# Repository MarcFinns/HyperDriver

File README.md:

# HyperDriver
LED driver and power board for Hyperion (DYI Ambilight)

See short video: https://www.youtube.com/watch?v=JoaK5aRHBMA

After setting up hyperion I was annoyed by starting/stopping it manually every time.
My weekend project was to build a proper solution - with components I had in the drawer, which might explain some weird design choices.

The board does the following:

* Connects as a PI hat
* Powers the PI and the LED strip with the same power supply
* Provides 5V drivers / level adaptation for the APA 102 LED stripe
* Allows to turn the PI on by pushing a button
* With the same button, triggers a proper shutdown (no abrupt power cut)
* Connects to TV via USB and can start the PI when the TV turns on
* The PI can automatically shutdown when TV goes off (immediately or after X minutes)
* If the automatic turn on from TV is triggered, the PI can still be shut down via the button
* A 5V socket is available for a small fan, in case

The On/Off function is proper, meaning the power supply is truly disconnected from the mains when off.
I made sure that the PCB is single side and doable at home with some medium skills (e.g. i made it with toner transfer). 
I could not avoid one SMD but only because I did not have the through-hole part in the drawer. Convertinf the PCB to through hole is trivial.
The whole thing fits in a small electric junction box. See pictures.

**IMPORTANT DISCLAIMER:**<BR>
* This is **NOT** your typical 5V Arduino project. <BR>
* It is **NOT** breadboard friendly.<BR>
* Make it **ONLY** if you know what you are doing.<BR>
* Danger of electrocution

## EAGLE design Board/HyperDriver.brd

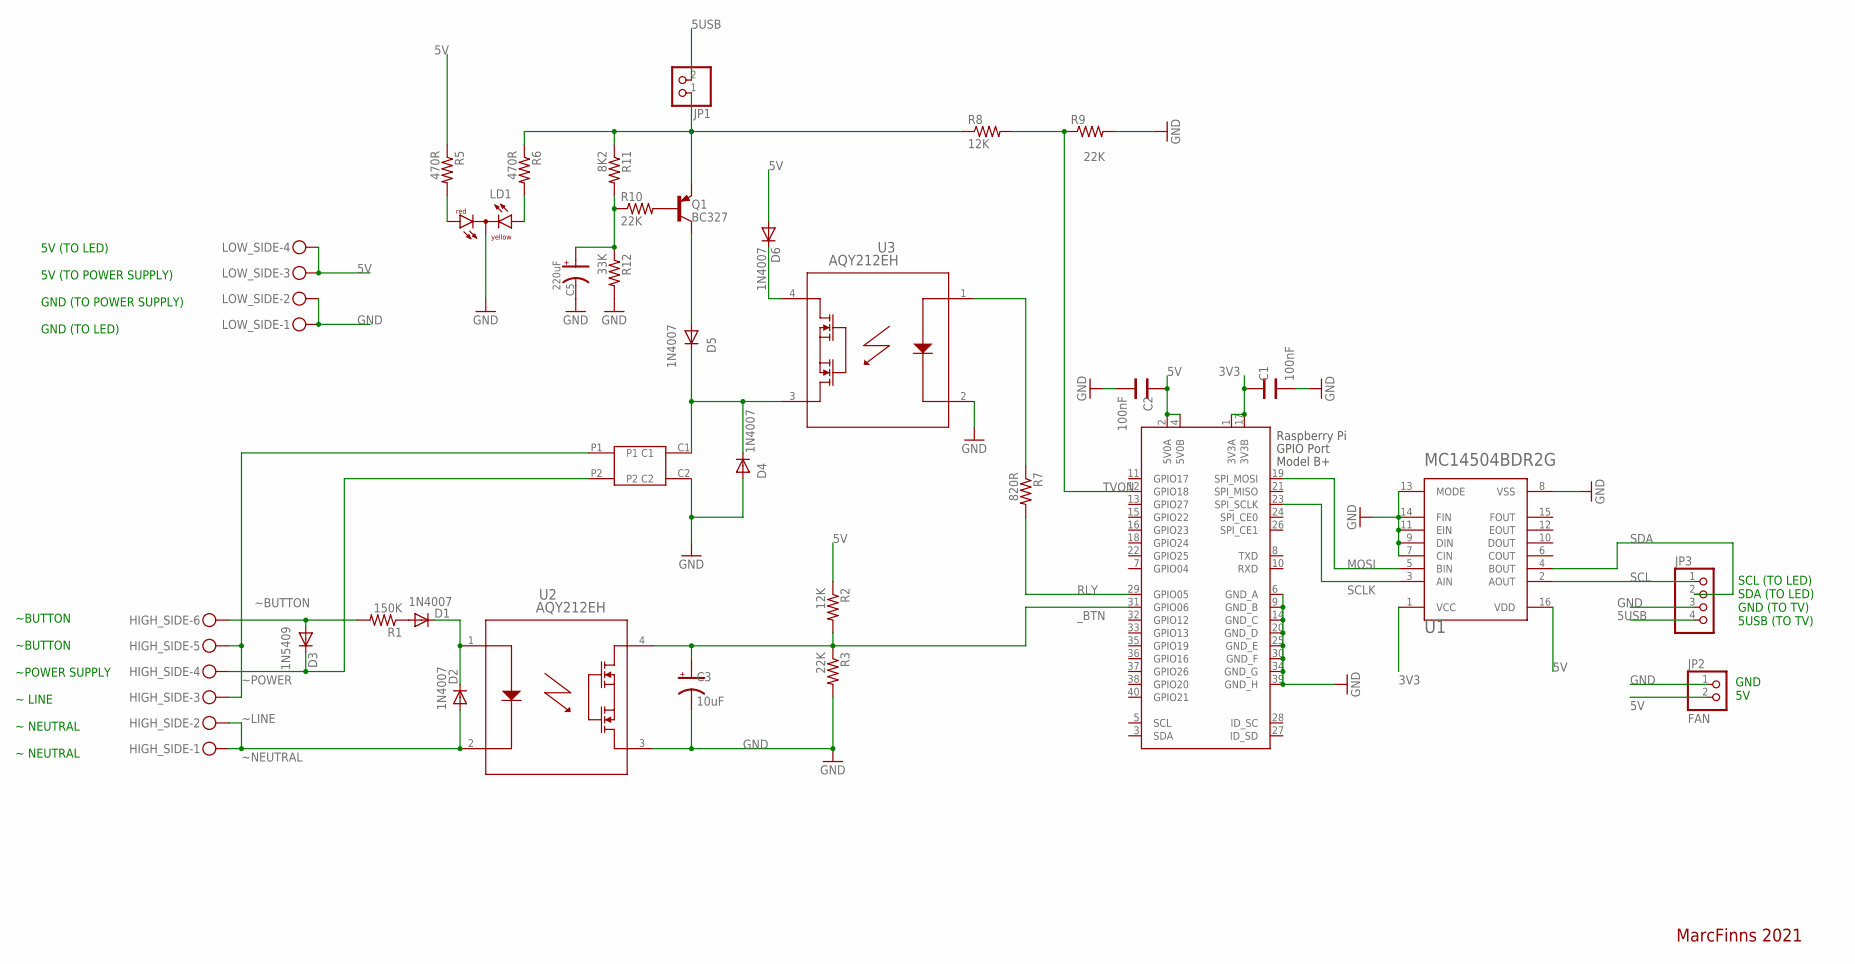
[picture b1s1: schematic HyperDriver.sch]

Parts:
C1, C2: 100nF; CAP-055X070
C3: 10uF; CAP-POL-025X50
C5: 220uF; CAP-POL-E3,5-8
D1, D2, D4, D5, D6: 1N4007; DO41-10
D3: 1N5409; DO201-15
G5NB_RELAY1: OMRON_G5NB_RELAY; G5NB_RELAY
HIGH_SIDE: MKDSN1,5/6-5,08
JP1: PINHD-1X2; 1X02
JP2: FAN; 1X02
JP3: PINHD-1X4; 1X04
LD1: DUOLED-RY-C; DUOLED-C-5MM
LOW_SIDE: MKDSN1,5/4-5,08
Q1: BC327; TO92
R1: 150K; 0207/9
R2, R8: 12K; 0207/9
R3, R9, R10: 22K; 0207/9
R5, R6: 470R; 0207/9
R7: 820R; 0207/9
R11: 8K2; 0207/9
R12: 33K; 0207/9
U1: ON_SEMICONDUCTOR_MC14504BDR2GON_SEMICONDUCTOR_MC1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; ON_SEMICONDUCTOR_MC14504BDR2G_1
U2, U3: AQY212EH; PAN_AQY21-DIP4_PAN
X1: RASPI_GPIO_B+#_PIN; RASPI_GPIO_B+_PIN

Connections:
3V3: C1.1, U1.1 (VCC), X1.1 (3V3A), X1.17 (3V3B)
5USB: JP1.2, JP3.4
5V: C2.1, D6.A, JP2.2, LOW_SIDE.3, LOW_SIDE.4, R2.1, R5.1, U1.16 (VDD), X1.2 (5V0A), X1.4 (5V0B)
GND: C1.2, C2.2, C3.C, C5.C, D4.A, G5NB_RELAY1.C2, JP2.1, JP3.3, LD1.C, LOW_SIDE.1, LOW_SIDE.2, R3.2, R9.2, R12.2, U1.7 (CIN), U1.8 (VSS), U1.9 (DIN), U1.11 (EIN), U1.13 (MODE), U1.14 (FIN), U2.3, U3.2, X1.6 (GND_A), X1.9 (GND_B), X1.14 (GND_C), X1.20 (GND_D), X1.25 (GND_E), X1.30 (GND_F), X1.34 (GND_G), X1.39 (GND_H)
J_5USB: JP1.1, Q1.1 (E), R6.1, R8.1, R11.1
MOSI: U1.5 (BIN), X1.19 (SPI_MOSI)
unnamed: LD1.AR, R5.2
unnamed: LD1.AX (AY), R6.2
unnamed: D6.C, U3.4
unnamed: Q1.2 (B), R10.2
unnamed: C5.A, R10.1, R11.2, R12.1
unnamed: D1.C, D2.C, U2.1
unnamed: R7.1, U3.1
unnamed: D4.C, D5.C, G5NB_RELAY1.C1, U3.3
unnamed: D5.A, Q1.3 (C)
unnamed: D1.A, R1.1
RLY: R7.2, X1.29 (GPIO05)
SCL: JP3.1, U1.2 (AOUT)
SCLK: U1.3 (AIN), X1.23 (SPI_SCLK)
SDA: JP3.2, U1.4 (BOUT)
TVON: R8.2, R9.1, X1.12 (GPIO18)
_BTN: C3.A, R2.2, R3.1, U2.4, X1.31 (GPIO06)
~BUTTON: D3.A, HIGH_SIDE.6, R1.2
~LINE: G5NB_RELAY1.P1, HIGH_SIDE.3, HIGH_SIDE.5
~NEUTRAL: D2.A, HIGH_SIDE.1, HIGH_SIDE.2, U2.2
~POWER: D3.C, G5NB_RELAY1.P2, HIGH_SIDE.4

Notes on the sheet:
SCL (TO LED) SDA (TO LED) GND (TO TV) 5USB (TO TV)
GND 5V
~BUTTON ~BUTTON ~POWER SUPPLY ~ LINE ~ NEUTRAL ~ NEUTRAL
5V (TO LED) 5V (TO POWER SUPPLY) GND (TO POWER SUPPLY) GND (TO LED)
MarcFinns 2021

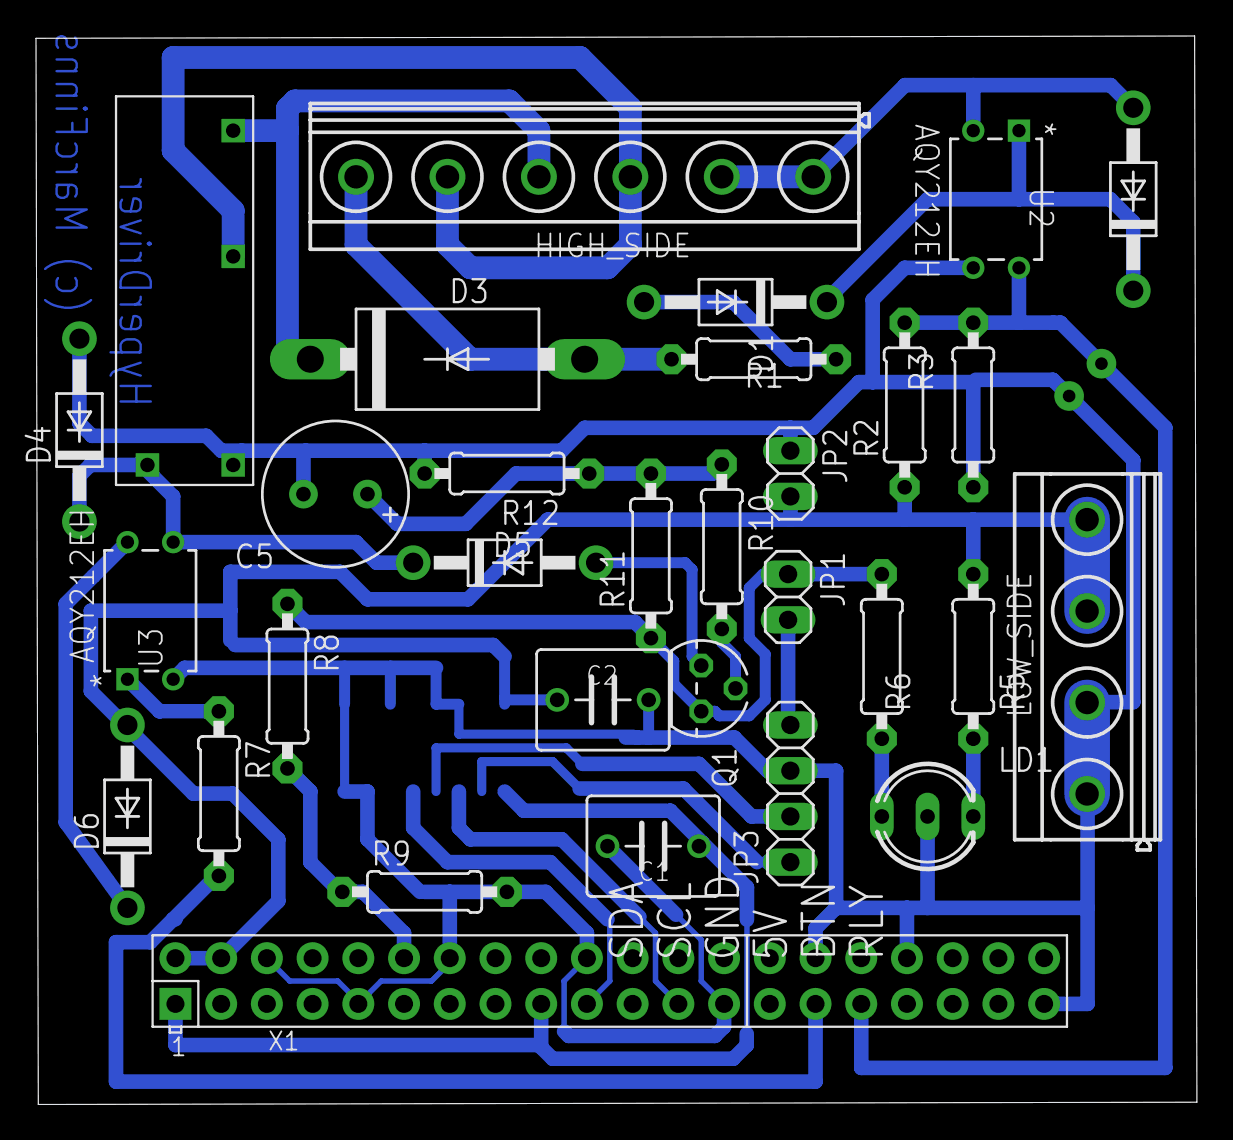
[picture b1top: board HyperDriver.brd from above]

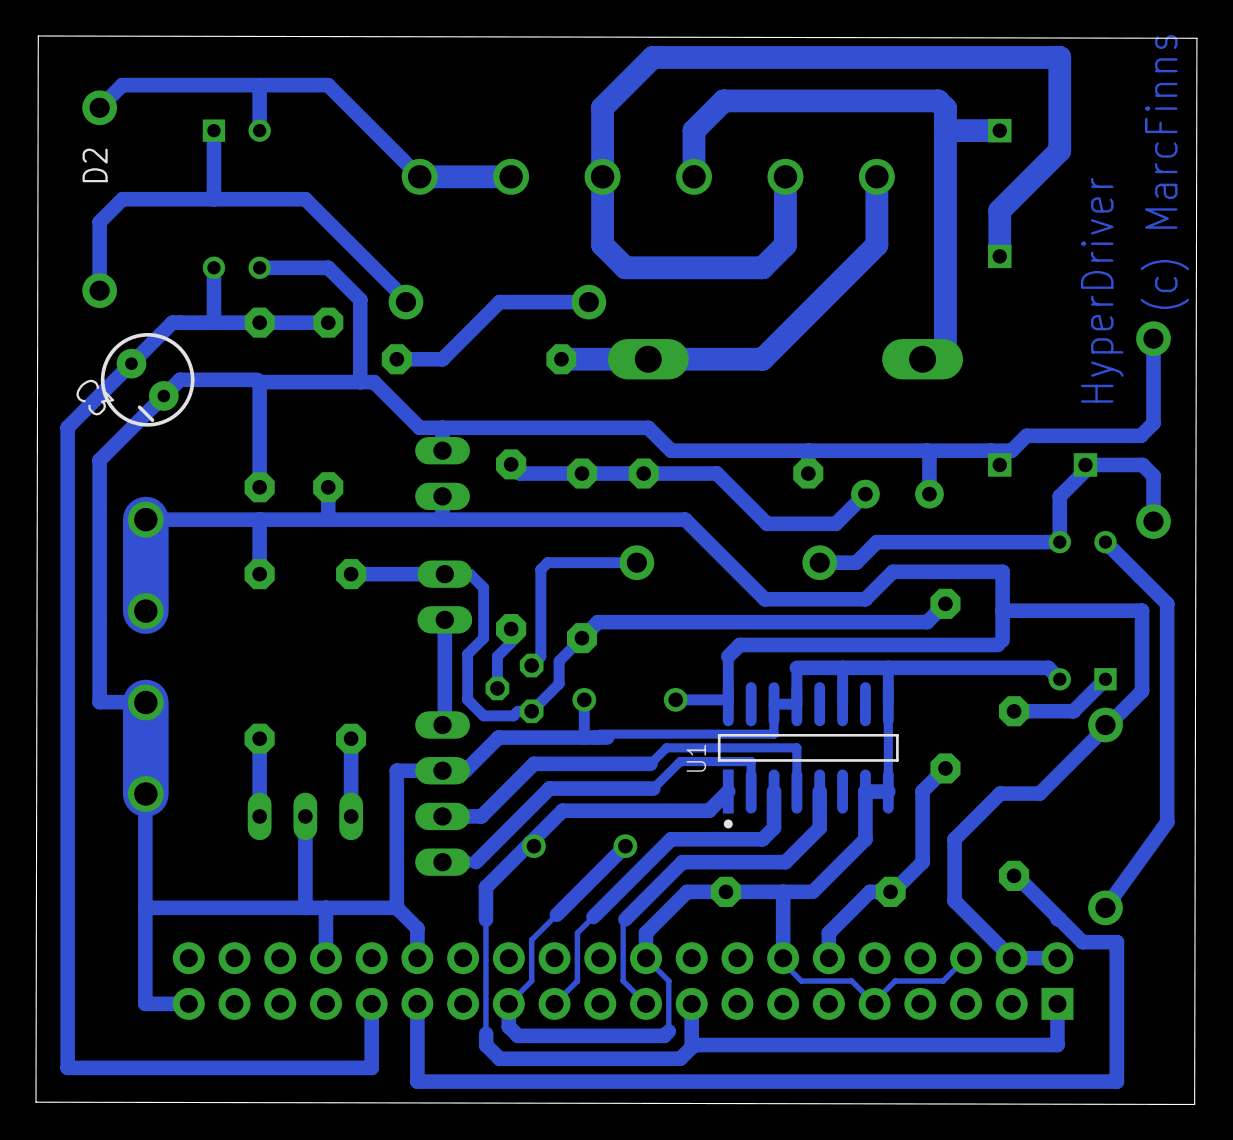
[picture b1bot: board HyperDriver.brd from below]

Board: 2 copper layers, 64.5 x 59.4 mm, 33 parts (2 on the bottom side), 26 nets.

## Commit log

2021-03-22 Update crontab
2021-03-22 Add files via upload
    corrected a C value
